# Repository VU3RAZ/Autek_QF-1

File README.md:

# Autek QF-1 Audio Filter: redraw, KiCad rebuild and analysis

A modern rework of the 1970s **Autek Research QF-1** tunable audio filter (peak / notch / low-pass, 250 Hz–2.5 kHz), made from the original 3-page manual.

| What | Where |
|---|---|
| Redrawn manual: full text plus vector schematics, hookup diagram and response curves | [`docs/Autek_QF-1_Instructions_Redrawn.pdf`](docs/Autek_QF-1_Instructions_Redrawn.pdf) |
| How the circuit works, stage by stage, with a performance rating | [`docs/QF1_How_It_Works.md`](docs/QF1_How_It_Works.md) |
| KiCad 7 projects: wired schematics plus routed 2-layer through-hole PCBs | [`kicad/`](kicad/) (see [`kicad/README.md`](kicad/README.md)) |
| Preview of both boards (schematics, copper, assembly) | [`docs/QF1_KiCad_Overview.pdf`](docs/QF1_KiCad_Overview.pdf) |
| Gerbers and drill files, ready for a PCB fab | `kicad/*/fab/*-gerbers.zip` |
| BOMs | `kicad/*/docs/*-BOM.csv` |
| LTspice / SPICE simulation: both boards and the complete unit, plus an `.asc` schematic generator | [`ltspice/`](ltspice/) |
| Python generators (PDF redraw, schematics, PCB placement and routing) | [`tools/`](tools/) |

Original manual scan: <https://vtda.org/docs/radio/Autek/Autek_QF-1.pdf>

## Boards

- **QF1_Main_Filter** (114 × 84 mm): two cascaded state-variable filter sections (TL072 × 3, replacing the µA747) and the U4 output amp (TL071, replacing the µA741). Board pins 1–21 keep the original numbering for front-panel wiring.
- **QF1_Amp_Supply** (92 × 64 mm): a Sallen-Key low-pass driver, a BC337/BC327 push-pull output, and a bridge-rectified supply fed from 12–15 VAC off-board.

Both boards are fully routed. DRC shows 0 errors. Netlist and pad connectivity are verified against the original circuit.

## Before ordering boards

See [`kicad/README.md`](kicad/README.md). In particular: the values chosen on test (R3/R5/R10/R11, R4/R9), C9/C10 left unfitted (DNP), the screw-terminal wire-entry orientation, and running ERC once in KiCad.

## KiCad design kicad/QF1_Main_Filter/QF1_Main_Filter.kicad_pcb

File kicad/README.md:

# Autek QF-1 Audio Filter: KiCad 7 projects

Two KiCad 7 projects recreated from the original Autek QF-1 manual schematics.
Each has a wired schematic laid out like the original drawing and a routed 2-layer through-hole PCB.

| Folder | Board | Size |
|---|---|---|
| `QF1_Main_Filter/` | Main filter board: two cascaded state-variable sections (U1 to U3) and output amp U4 | 114 x 84 mm |
| `QF1_Amp_Supply/` | Audio power amp (Sallen-Key + BC337/BC327 follower) and DC supply | 92 x 64 mm |

Each folder contains:
- `*.kicad_pro`, `*.kicad_sch`, `*.kicad_pcb`: open the `.kicad_pro` in KiCad 7 or later.
- `QF1.kicad_sym` and `sym-lib-table`: the project-local `B+` power symbol.
- `fab/*-gerbers.zip`: Gerbers (both copper layers, mask, silkscreen, outline), Excellon drill file and job file, ready to upload to a PCB fab.
- `docs/`: schematic PDF, top/bottom copper PDFs, assembly drawing, BOM (CSV) and DRC report.

## Checks performed
- Schematic connectivity: the netlist KiCad exports from each schematic was compared net by net against the circuit traced from the original manual. Both match exactly.
- PCB: every pad's net matches the original circuit. Freerouting routed 100% (0 unconnected pads, no vias needed). DRC shows **0 errors**; only cosmetic silkscreen-overlap warnings remain.
- KiCad 7's command-line tool has no ERC command. Run *Inspect > Electrical Rules Checker* once in your KiCad. Expect at most "dangling wire end" notes where the original drawing's rails end.

## Changes from the 1970s original
- **U1, U2, U3: TL072** (dual, 8-pin) replace the µA747 (dual, 14-pin). The A/B halves keep the original U1A to U3B roles and pin labels on the schematic. U4 and U101 are **TL071** in place of the µA741 (same pinout).
- **Q101/Q102: BC337/BC327** replace MPS6560/MPS6562, using the wide-pitch TO-92 footprint (CBE order, as on the original layout).
- **Supply:** the mains transformer, ON-OFF switch and line caps C107/C108 are **off-board**. J101 takes 12 to 15 VAC from the transformer secondary (outer ends of the original centre-tapped winding; CT unused) or from an AC wall adapter. A 4-diode bridge (D102 to D105) replaces the original 2-diode centre-tap rectifier. C106 is uprated to 35 V.
- **Added:** C13 (47 µF), C14 and C15 (100 nF) supply decoupling on the main board, and C109 (100 nF) on the amp board.
- **Mounting:** H101 is a plated M3 hole on GND, the original "direct RF ground to chassis through screw". The other holes are unplated.

## Values to confirm on test (as the original notes say)
- R3, R5, R10, R11: fitted as 3.3K. The original says 3.3K to 6.8K, chosen to match C2 to C5 (C2 to C5 matched to 1 %). 3.3K gives a 217 Hz–2.68 kHz tuning range, covering the manual's 250–2500 Hz; 4.7K would top out at 1.88 kHz. Set the R8 trim to about 3.3K to align section 2. R11 also sets the low-pass mode gain (U4 gain 30, +29.6 dB).
- R4, R9: fitted as 4.7K. The original says "chosen to match select. pot" and gives no value; 4.7K is an estimate from the circuit, so adjust for the selectivity range you want.
- C9, C10: no value on the original (in parallel with R17/R14). Footprints are provided and marked DNP.
- C7: "not included in QF-1" (QF-2 output). Marked DNP.
- C2 to C5 are read as .018 µF (C3 is partly illegible on the scan).

## Panel wiring (unchanged; board pin numbers are on the silkscreen)
J1 = board pins 1 to 7, J2 = board pins 8 to 19, J3 = pin 20 (GND), J4 = pin 21 (QF-1 out).
- 5 and 6 tied to the front SELECTIVITY wiper; 8 to the top of front SELECTIVITY and to the front FREQUENCY wiper; 9 to the top of front FREQUENCY.
- 13 and 16 tied to the rear SELECTIVITY wiper; 18 to the top of rear SELECTIVITY and to the rear FREQUENCY wiper; 15 to the top of rear FREQUENCY.
- Pots are dual 500K (front/rear sections); bottom terminals are left open. Clockwise rotation selects lower frequency.
- Function switch pole 1: common 12, PK 5, NTCH 10, LP 11. Pole 2: common 3, PK 19, NTCH 17, LP 14.
- Main board 21 goes to amp board IN; 20 and the amp board GND go to chassis; amp board B+ goes to main board 1.

## Please check before ordering boards
- **Screw terminal orientation:** J101/J102 are placed with the wire entry assumed on the deeper side of the KiCad footprint, so they face the board edges. Confirm in the 3D viewer.
- The routing is autorouted (Freerouting) and DRC-clean. Give it a visual once-over in KiCad and tidy any track you'd like shorter.

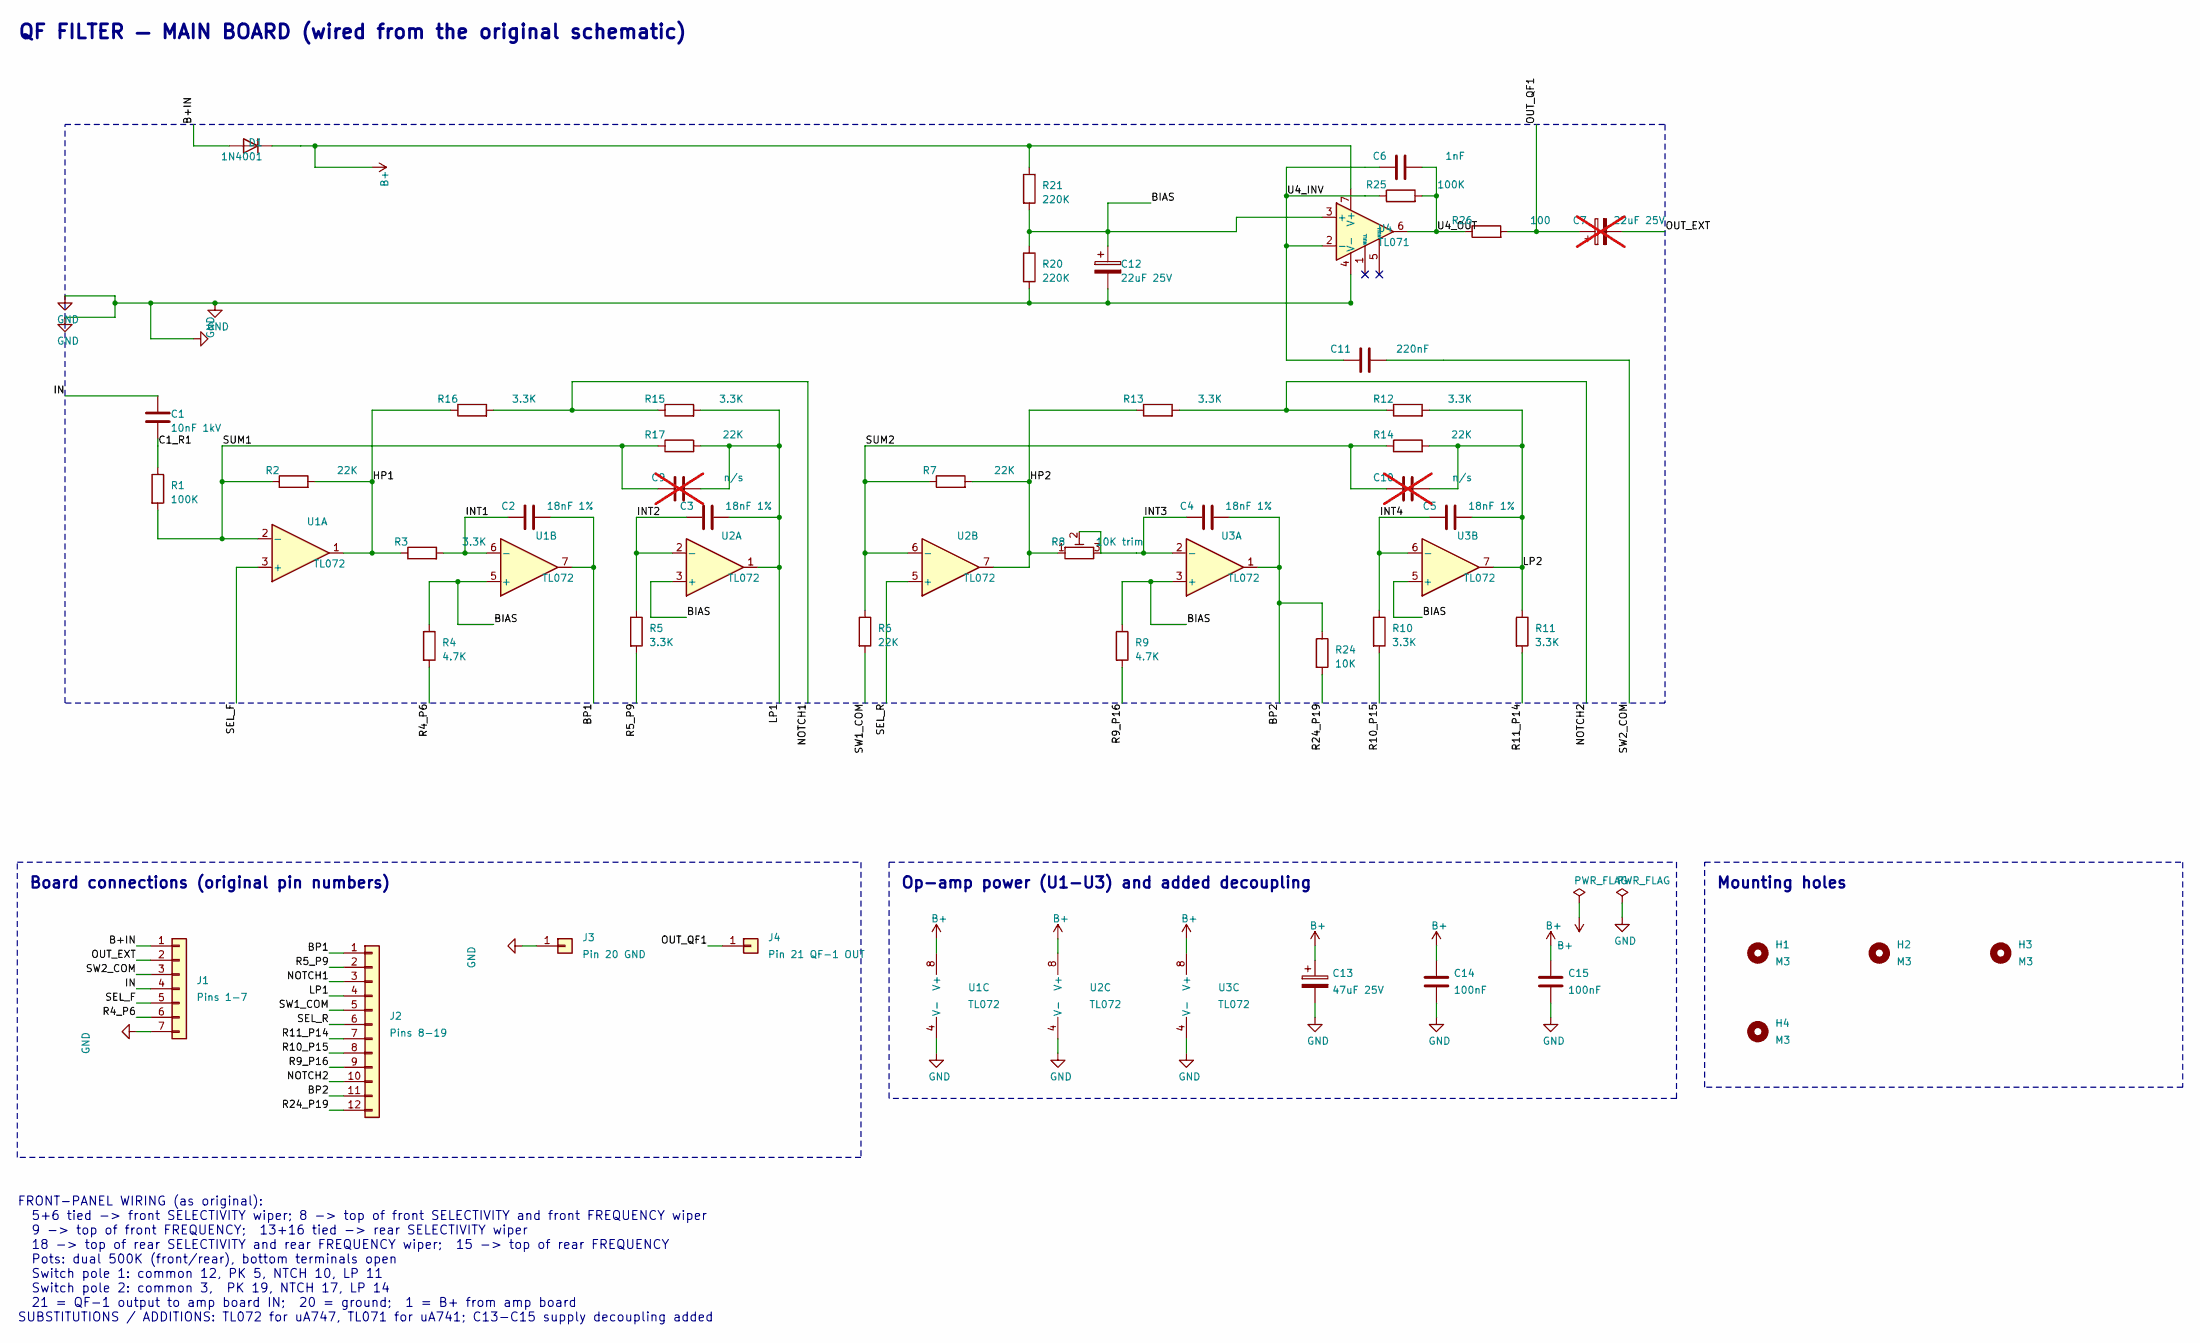
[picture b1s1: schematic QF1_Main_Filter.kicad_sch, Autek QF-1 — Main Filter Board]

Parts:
C1: 10nF 1kV; C_Disc_D7.5mm_W5.0mm_P5.00mm
C2, C3, C4, C5: 18nF 1%; C_Rect_L7.2mm_W3.5mm_P5.00mm_FKS2_FKP2_MKS2_MKP2
C6: 1nF; C_Disc_D5.0mm_W2.5mm_P5.00mm
C7: 22uF 25V; CP_Radial_D5.0mm_P2.00mm; not fitted
C9, C10: n/s; C_Disc_D5.0mm_W2.5mm_P5.00mm; not fitted
C11: 220nF; C_Rect_L7.2mm_W3.5mm_P5.00mm_FKS2_FKP2_MKS2_MKP2
C12: 22uF 25V; CP_Radial_D5.0mm_P2.00mm
C13: 47uF 25V; CP_Radial_D6.3mm_P2.50mm
C14, C15: 100nF; C_Disc_D5.0mm_W2.5mm_P5.00mm
D1: 1N4001; D_DO-41_SOD81_P10.16mm_Horizontal
H1, H2, H3, H4: M3; MountingHole_3.2mm_M3
J1: Pins 1-7; PinHeader_1x07_P2.54mm_Vertical
J2: Pins 8-19; PinHeader_1x12_P2.54mm_Vertical
J3: Pin 20 GND; PinHeader_1x01_P2.54mm_Vertical
J4: Pin 21 QF-1 OUT; PinHeader_1x01_P2.54mm_Vertical
R1, R25: 100K; R_Axial_DIN0207_L6.3mm_D2.5mm_P10.16mm_Horizontal
R2, R6, R7, R14, R17: 22K; R_Axial_DIN0207_L6.3mm_D2.5mm_P10.16mm_Horizontal
R3, R5, R10, R11, R12, R13, R15, R16: 3.3K; R_Axial_DIN0207_L6.3mm_D2.5mm_P10.16mm_Horizontal
R4, R9: 4.7K; R_Axial_DIN0207_L6.3mm_D2.5mm_P10.16mm_Horizontal
R8: 10K trim; Potentiometer_Bourns_3386P_Vertical
R20, R21: 220K; R_Axial_DIN0207_L6.3mm_D2.5mm_P10.16mm_Horizontal
R24: 10K; R_Axial_DIN0207_L6.3mm_D2.5mm_P10.16mm_Horizontal
R26: 100; R_Axial_DIN0207_L6.3mm_D2.5mm_P10.16mm_Horizontal
U1, U2, U3: TL072; DIP-8_W7.62mm
U4: TL071; DIP-8_W7.62mm

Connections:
B+: C13.1, C14.1, C15.1, D1.1 (K), R21.1, U1.8 (V+), U2.8 (V+), U3.8 (V+), U4.7 (V+)
B+IN: D1.2 (A), J1.1
BIAS: C12.1, R4.1, R9.1, R20.1, R21.2, U1.5 (+), U2.3 (+), U3.3 (+), U3.5 (+), U4.3 (+)
BP1: C2.2, J2.1, U1.7
BP2: C4.2, J2.11, R24.1, U3.1
C1_R1: C1.2, R1.1
GND: C12.2, C13.2, C14.2, C15.2, J1.7, J3.1, R20.2, U1.4 (V-), U2.4 (V-), U3.4 (V-), U4.4 (V-)
HP1: R2.2, R3.1, R16.1, U1.1
HP2: R7.2, R8.1, R13.1, U2.7
IN: C1.1, J1.4
INT1: C2.1, R3.2, U1.6 (-)
INT2: C3.1, R5.1, U2.2 (-)
INT3: C4.1, R8.2, R8.3, U3.2 (-)
INT4: C5.1, R10.1, U3.6 (-)
LP1: C3.2, C9.2, J2.4, R15.2, R17.2, U2.1
LP2: C5.2, C10.2, R11.1, R12.2, R14.2, U3.7
NOTCH1: J2.3, R15.1, R16.2
NOTCH2: J2.10, R12.1, R13.2
OUT_EXT: C7.2, J1.2
OUT_QF1: C7.1, J4.1, R26.2
R4_P6: J1.6, R4.2
R5_P9: J2.2, R5.2
R9_P16: J2.9, R9.2
R10_P15: J2.8, R10.2
R11_P14: J2.7, R11.2
R24_P19: J2.12, R24.2
SEL_F: J1.5, U1.3 (+)
SEL_R: J2.6, U2.5 (+)
SUM1: C9.1, R1.2, R2.1, R17.1, U1.2 (-)
SUM2: C10.1, R6.1, R7.1, R14.1, U2.6 (-)
SW1_COM: J2.5, R6.2
SW2_COM: C11.2, J1.3
U4_INV: C6.1, C11.1, R25.1, U4.2 (-)
U4_OUT: C6.2, R25.2, R26.1, U4.6

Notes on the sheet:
QF FILTER — MAIN BOARD (wired from the original schematic)
Board connections (original pin numbers)
Op-amp power (U1-U3) and added decoupling
Mounting holes
FRONT-PANEL WIRING (as original): 5+6 tied -> front SELECTIVITY wiper; 8 -> top of front SELECTIVITY and front FREQUENCY wiper 9 -> top of front FREQUENCY; 13+16 tied -> rear SELECTIVITY wiper 18 -> top of rear SELECTIVITY and rear FREQUENCY wiper; 15 -> top of rear FREQUENCY Pots: dual 500K (front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

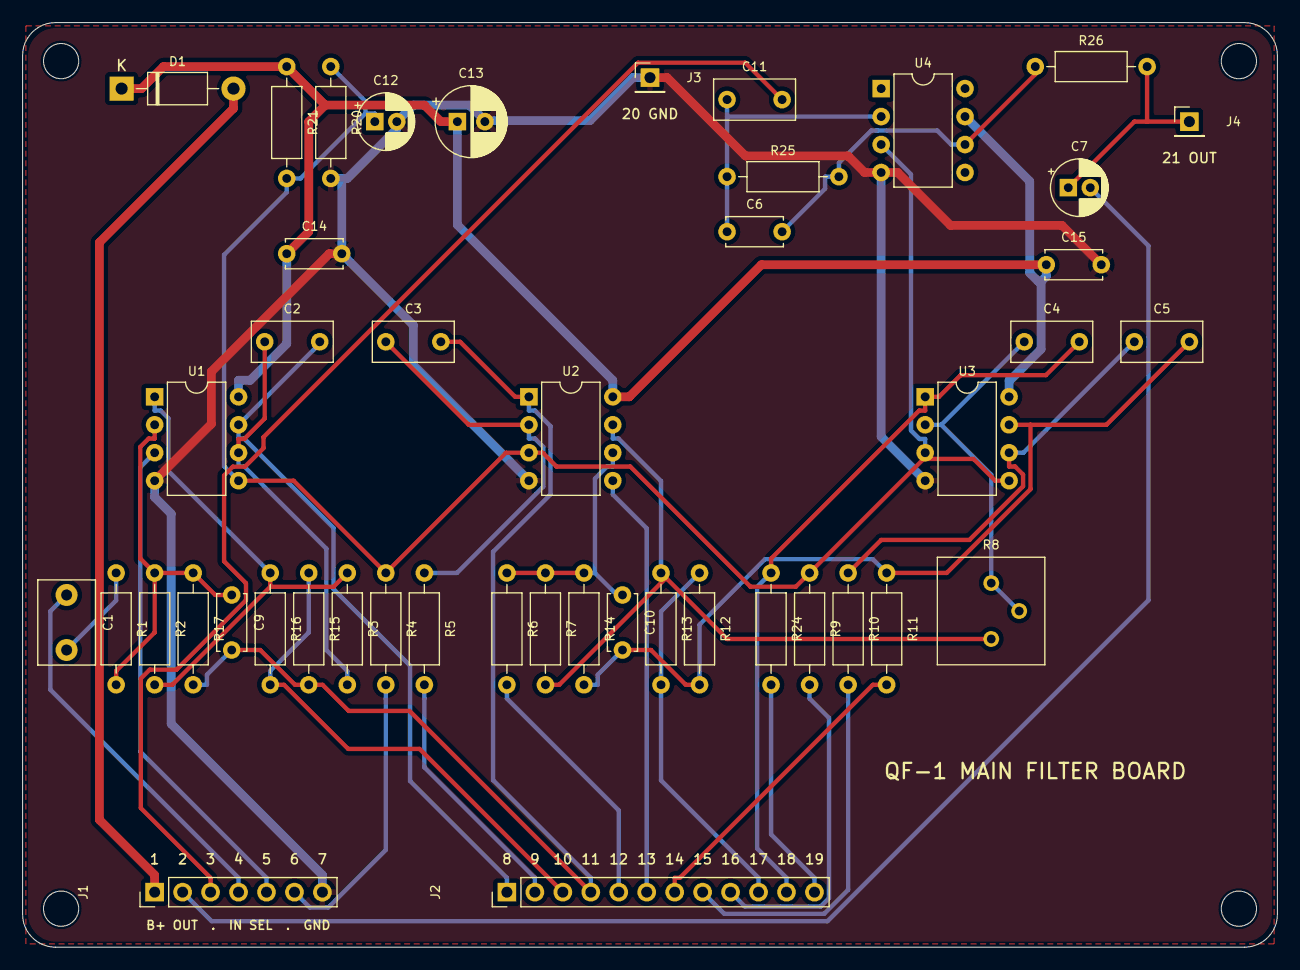
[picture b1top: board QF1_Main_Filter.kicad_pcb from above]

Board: 2 copper layers, 114.0 x 84.0 mm, 49 parts (0 on the bottom side), 34 nets.

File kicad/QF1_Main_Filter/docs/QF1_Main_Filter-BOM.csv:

Qty,References,Value,Footprint,Fit,Notes
1,C1,10nF 1kV,C_Disc_D7.5mm_W5.0mm_P5.00mm,fit,
4,C2 C3 C4 C5,18nF 1%,C_Rect_L7.2mm_W3.5mm_P5.00mm_FKS2_FKP2_MKS2_MKP2,fit,
1,C6,1nF,C_Disc_D5.0mm_W2.5mm_P5.00mm,fit,
1,C7,22uF 25V,CP_Radial_D5.0mm_P2.00mm,DNP,not included in QF-1
2,C9 C10,n/s,C_Disc_D5.0mm_W2.5mm_P5.00mm,DNP,value not given on original; optional
1,C11,220nF,C_Rect_L7.2mm_W3.5mm_P5.00mm_FKS2_FKP2_MKS2_MKP2,fit,
1,C12,22uF 25V,CP_Radial_D5.0mm_P2.00mm,fit,
1,C13,47uF 25V,CP_Radial_D6.3mm_P2.50mm,fit,added: B+ bulk decoupling (not on original)
1,C14,100nF,C_Disc_D5.0mm_W2.5mm_P5.00mm,fit,added: decoupling U1/U2
1,C15,100nF,C_Disc_D5.0mm_W2.5mm_P5.00mm,fit,added: decoupling U3/U4
1,D1,1N4001,D_DO-41_SOD81_P10.16mm_Horizontal,fit,
1,J1,Pins 1-7,PinHeader_1x07_P2.54mm_Vertical,fit,"Board pins 1 B+in, 2 out (not QF-1), 3 sw2 com, 4 input, 5/6 front select, 7 gnd"
1,J2,Pins 8-19,PinHeader_1x12_P2.54mm_Vertical,fit,J2 pin n = original board pin n+7
1,J3,Pin 20 GND,PinHeader_1x01_P2.54mm_Vertical,fit,
1,J4,Pin 21 QF-1 OUT,PinHeader_1x01_P2.54mm_Vertical,fit,
2,R1 R25,100K,R_Axial_DIN0207_L6.3mm_D2.5mm_P10.16mm_Horizontal,fit,
5,R2 R6 R7 R14 R17,22K,R_Axial_DIN0207_L6.3mm_D2.5mm_P10.16mm_Horizontal,fit,
3,R3 R5 R10,3.3K,R_Axial_DIN0207_L6.3mm_D2.5mm_P10.16mm_Horizontal,fit,"3.3K-6.8K, matched to C2-C5"
2,R4 R9,4.7K,R_Axial_DIN0207_L6.3mm_D2.5mm_P10.16mm_Horizontal,fit,select to match selectivity pot
1,R8,10K trim,Potentiometer_Bourns_3386P_Vertical,fit,alignment trim (rheostat)
1,R11,3.3K,R_Axial_DIN0207_L6.3mm_D2.5mm_P10.16mm_Horizontal,fit,3.3K-6.8K
4,R12 R13 R15 R16,3.3K,R_Axial_DIN0207_L6.3mm_D2.5mm_P10.16mm_Horizontal,fit,
2,R20 R21,220K,R_Axial_DIN0207_L6.3mm_D2.5mm_P10.16mm_Horizontal,fit,
1,R24,10K,R_Axial_DIN0207_L6.3mm_D2.5mm_P10.16mm_Horizontal,fit,
1,R26,100,R_Axial_DIN0207_L6.3mm_D2.5mm_P10.16mm_Horizontal,fit,
3,U1 U2 U3,TL072,DIP-8_W7.62mm,fit,replaces µA747
1,U4,TL071,DIP-8_W7.62mm,fit,replaces µA741

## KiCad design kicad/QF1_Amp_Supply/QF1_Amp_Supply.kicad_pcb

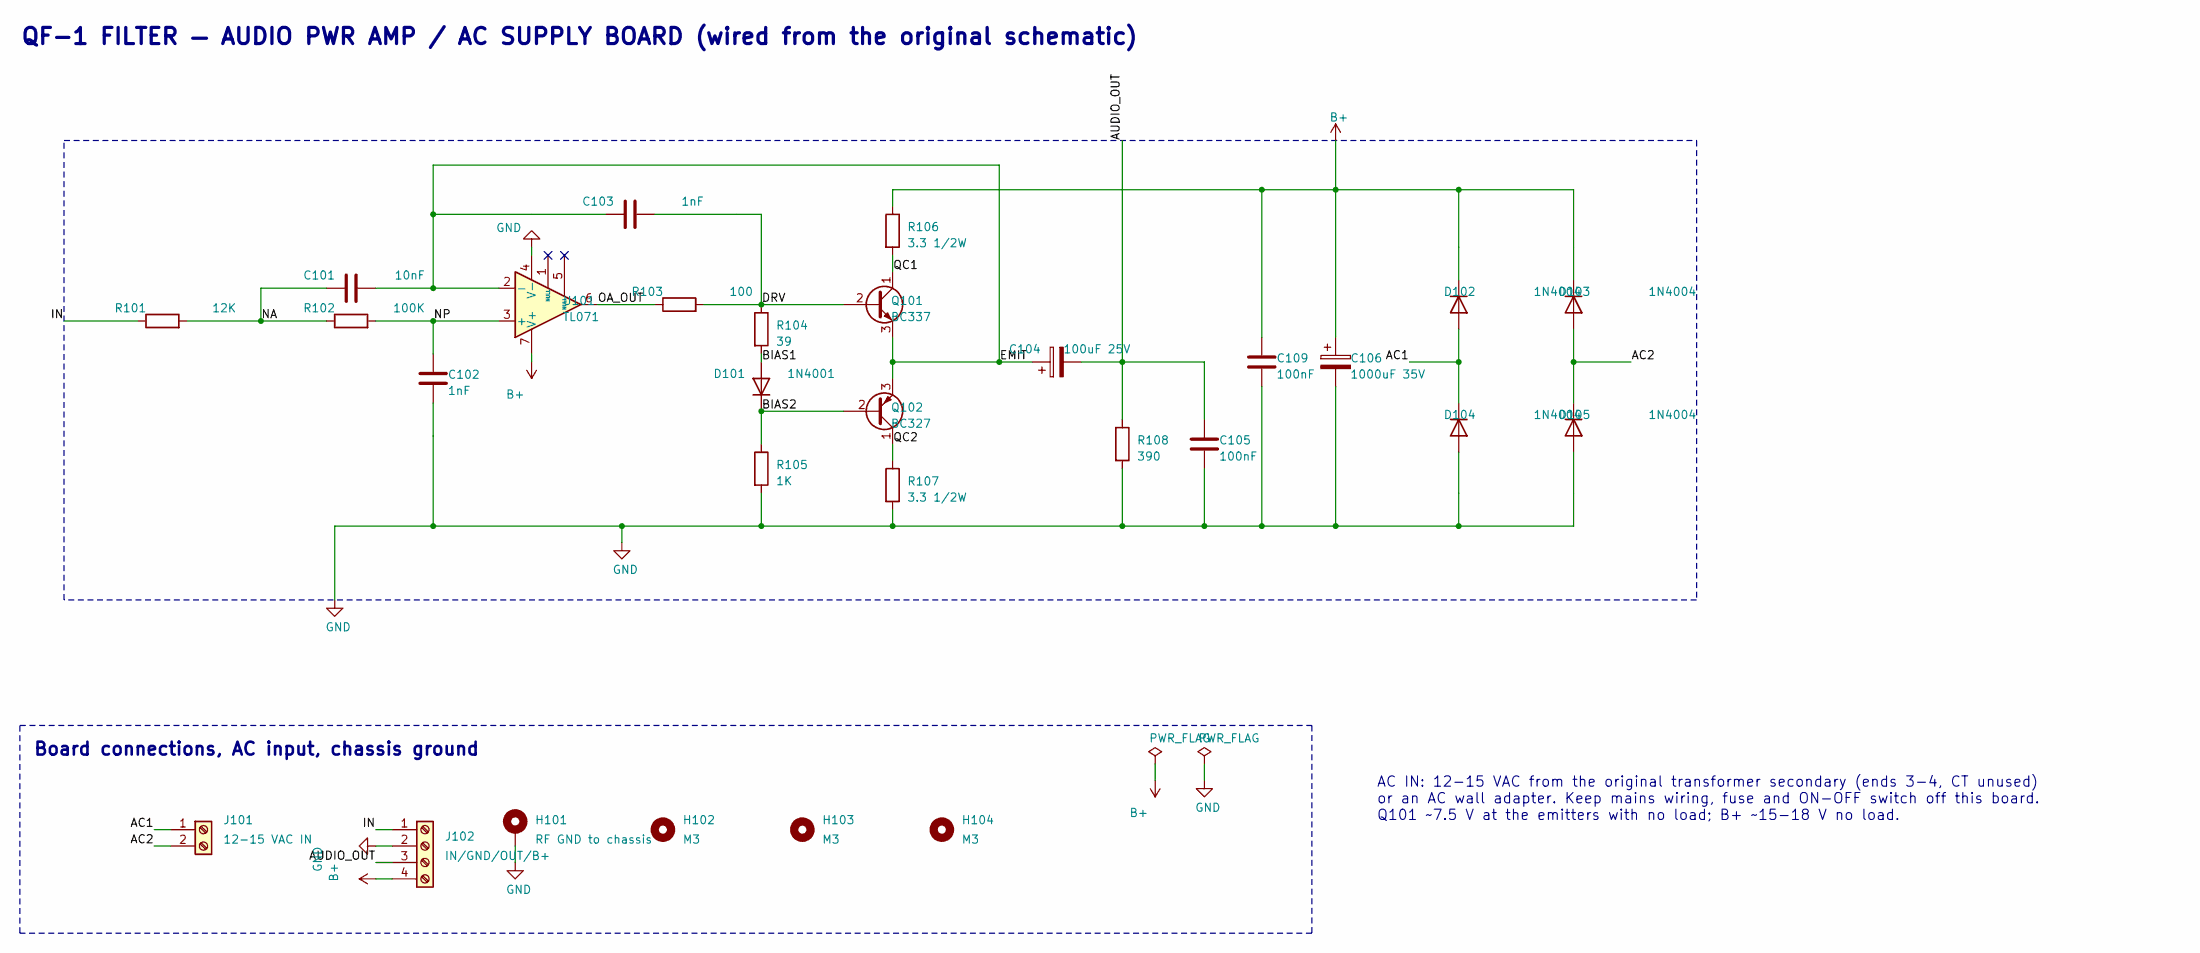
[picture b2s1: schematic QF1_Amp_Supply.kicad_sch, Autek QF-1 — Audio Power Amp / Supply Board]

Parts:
C101: 10nF; C_Rect_L7.2mm_W3.5mm_P5.00mm_FKS2_FKP2_MKS2_MKP2
C102, C103: 1nF; C_Disc_D5.0mm_W2.5mm_P5.00mm
C104: 100uF 25V; CP_Radial_D6.3mm_P2.50mm
C105, C109: 100nF; C_Disc_D5.0mm_W2.5mm_P5.00mm
C106: 1000uF 35V; CP_Radial_D12.5mm_P5.00mm
D101: 1N4001; D_DO-41_SOD81_P10.16mm_Horizontal
D102, D103, D104, D105: 1N4004; D_DO-41_SOD81_P10.16mm_Horizontal
H101: RF GND to chassis; MountingHole_3.2mm_M3_Pad_Via
H102, H103, H104: M3; MountingHole_3.2mm_M3
J101: 12-15 VAC IN; TerminalBlock_Phoenix_MKDS-1,5-2-5.08_1x02_P5.08mm_Horizont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
J102: IN/GND/OUT/B+; TerminalBlock_Phoenix_MKDS-1,5-4-5.08_1x04_P5.08mm_Horizont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
Q101: BC337; TO-92_Inline_Wide
Q102: BC327; TO-92_Inline_Wide
R101: 12K; R_Axial_DIN0207_L6.3mm_D2.5mm_P10.16mm_Horizontal
R102: 100K; R_Axial_DIN0207_L6.3mm_D2.5mm_P10.16mm_Horizontal
R103: 100; R_Axial_DIN0207_L6.3mm_D2.5mm_P10.16mm_Horizontal
R104: 39; R_Axial_DIN0207_L6.3mm_D2.5mm_P10.16mm_Horizontal
R105: 1K; R_Axial_DIN0207_L6.3mm_D2.5mm_P10.16mm_Horizontal
R106, R107: 3.3 1/2W; R_Axial_DIN0309_L9.0mm_D3.2mm_P12.70mm_Horizontal
R108: 390; R_Axial_DIN0207_L6.3mm_D2.5mm_P10.16mm_Horizontal
U101: TL071; DIP-8_W7.62mm

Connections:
AC1: D102.2 (A), D104.1 (K), J101.1
AC2: D103.2 (A), D105.1 (K), J101.2
AUDIO_OUT: C104.2, C105.1, J102.3, R108.1
B+: C106.1, C109.1, D102.1 (K), D103.1 (K), J102.4, R106.1, U101.7 (V+)
BIAS1: D101.2 (A), R104.2
BIAS2: D101.1 (K), Q102.2 (B), R105.1
DRV: C103.2, Q101.2 (B), R103.2, R104.1
EMIT: C101.2, C103.1, C104.1, Q101.3 (E), Q102.3 (E), U101.2 (-)
GND: C102.2, C105.2, C106.2, C109.2, D104.2 (A), D105.2 (A), H101.1, J102.2, R105.2, R107.2, R108.2, U101.4 (V-)
IN: J102.1, R101.1
NA: C101.1, R101.2, R102.1
NP: C102.1, R102.2, U101.3 (+)
OA_OUT: R103.1, U101.6
QC1: Q101.1 (C), R106.2
QC2: Q102.1 (C), R107.1

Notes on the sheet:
QF-1 FILTER — AUDIO PWR AMP / AC SUPPLY BOARD (wired from the original schematic)
Board connections, AC input, chassis ground
AC IN: 12-15 VAC from the original transformer secondary (ends 3-4, CT unused) or an AC wall adapter. Keep mains wiring, fuse and ON-OFF switch off this board. Q101 ~7.5 V at the emitters with no load; B+ ~15-18 V no load.

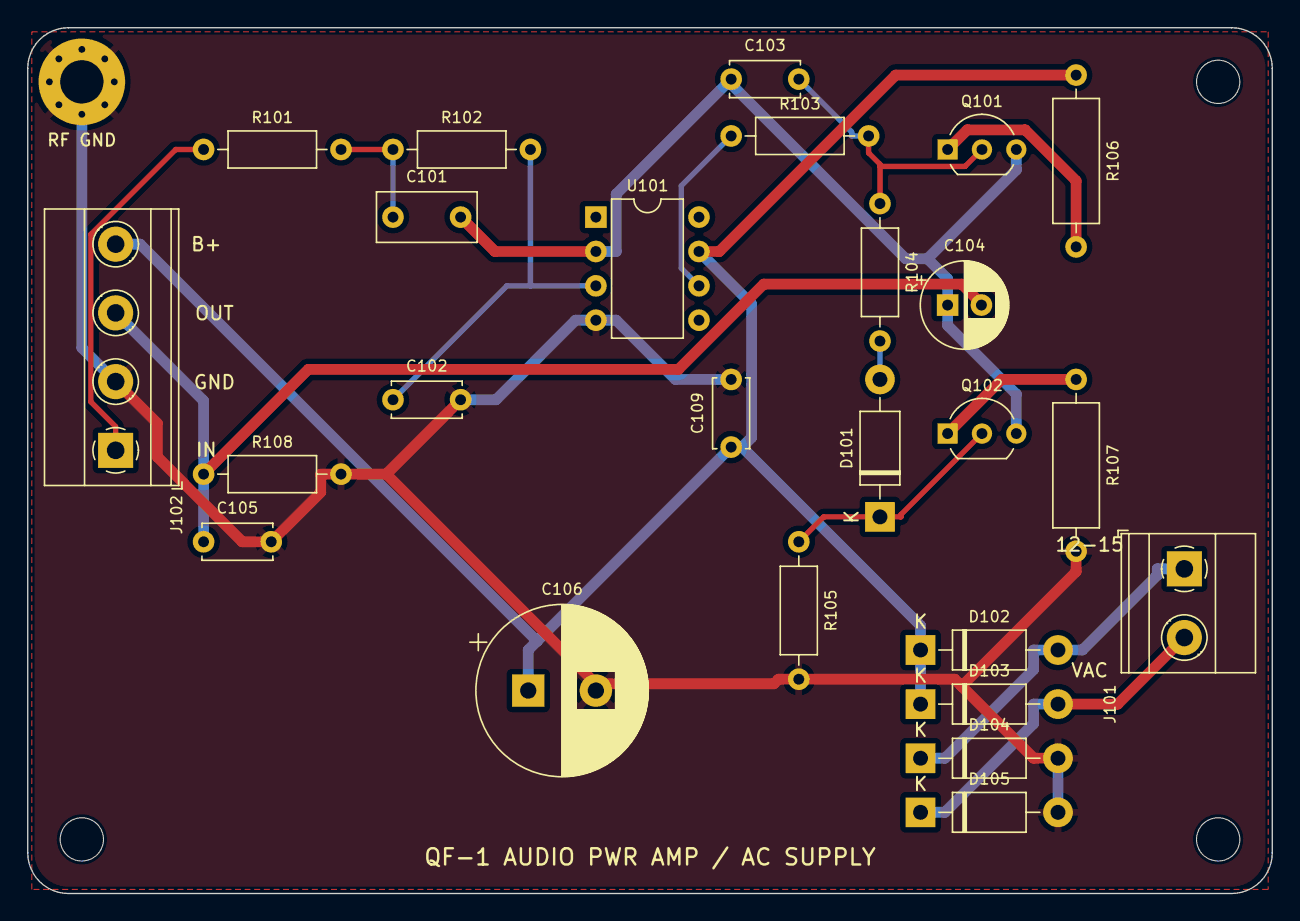
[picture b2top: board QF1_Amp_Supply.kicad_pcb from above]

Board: 2 copper layers, 92.0 x 64.0 mm, 29 parts (0 on the bottom side), 15 nets.

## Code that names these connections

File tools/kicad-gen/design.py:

"""Netlists for the two Autek QF-1 boards, as traced from the original schematics.
Each part: ref -> dict(sym, value, fp, pins={pin_number: net}, [dnp, note, group])."""

R07 = "Resistor_THT:R_Axial_DIN0207_L6.3mm_D2.5mm_P10.16mm_Horizontal"
R09 = "Resistor_THT:R_Axial_DIN0309_L9.0mm_D3.2mm_P12.70mm_Horizontal"
CFILM = "Capacitor_THT:C_Rect_L7.2mm_W3.5mm_P5.00mm_FKS2_FKP2_MKS2_MKP2"
CDISC = "Capacitor_THT:C_Disc_D5.0mm_W2.5mm_P5.00mm"
CHV = "Capacitor_THT:C_Disc_D7.5mm_W5.0mm_P5.00mm"
DIODE = "Diode_THT:D_DO-41_SOD81_P10.16mm_Horizontal"
DIP8 = "Package_DIP:DIP-8_W7.62mm"
TO92 = "Package_TO_SOT_THT:TO-92_Inline_Wide"


def R(a, b, val, fp=R07, **kw):
    return dict(sym="Device:R", value=val, fp=fp, pins={"1": a, "2": b}, **kw)


def C(a, b, val, fp=CFILM, **kw):
    return dict(sym="Device:C", value=val, fp=fp, pins={"1": a, "2": b}, **kw)


def CP(p, n, val, fp, **kw):
    return dict(sym="Device:C_Polarized", value=val, fp=fp, pins={"1": p, "2": n}, **kw)


def D(a, k, val="1N4001", **kw):
    return dict(sym="Device:D", value=val, fp=DIODE, pins={"1": k, "2": a}, **kw)


# ----------------------------------------------------------------- MAIN BOARD
MAIN = dict(name="QF1_Main_Filter", title="Autek QF-1 — Main Filter Board", parts={})
P = MAIN["parts"]
# board pins 1-7 (J1) and 8-19 (J2), 20 (J3), 21 (J4) keep the original numbering
P["J1"] = dict(sym="Connector_Generic:Conn_01x07", value="Pins 1-7",
               fp="Connector_PinHeader_2.54mm:PinHeader_1x07_P2.54mm_Vertical",
               pins={"1": "B+IN", "2": "OUT_EXT", "3": "SW2_COM", "4": "IN", "5": "SEL_F",
                     "6": "R4_P6", "7": "GND"},
               note="Board pins 1 B+in, 2 out (not QF-1), 3 sw2 com, 4 input, 5/6 front select, 7 gnd")
j2 = {8: "BP1", 9: "R5_P9", 10: "NOTCH1", 11: "LP1", 12: "SW1_COM", 13: "SEL_R", 14: "R11_P14",
      15: "R10_P15", 16: "R9_P16", 17: "NOTCH2", 18: "BP2", 19: "R24_P19"}
P["J2"] = dict(sym="Connector_Generic:Conn_01x12", value="Pins 8-19",
               fp="Connector_PinHeader_2.54mm:PinHeader_1x12_P2.54mm_Vertical",
               pins={str(k - 7): v for k, v in j2.items()},
               note="J2 pin n = original board pin n+7")
P["J3"] = dict(sym="Connector_Generic:Conn_01x01", value="Pin 20 GND",
               fp="Connector_PinHeader_2.54mm:PinHeader_1x01_P2.54mm_Vertical", pins={"1": "GND"})
P["J4"] = dict(sym="Connector_Generic:Conn_01x01", value="Pin 21 QF-1 OUT",
               fp="Connector_PinHeader_2.54mm:PinHeader_1x01_P2.54mm_Vertical", pins={"1": "OUT_QF1"})

# supply and bias
P["D1"] = D("B+IN", "B+")
P["R21"] = R("B+", "BIAS", "220K")
P["R20"] = R("BIAS", "GND", "220K")
P["C12"] = CP("BIAS", "GND", "22uF 25V", "Capacitor_THT:CP_Radial_D5.0mm_P2.00mm")
P["C13"] = CP("B+", "GND", "47uF 25V", "Capacitor_THT:CP_Radial_D6.3mm_P2.50mm",
              note="added: B+ bulk decoupling (not on original)")
P["C14"] = C("B+", "GND", "100nF", CDISC, note="added: decoupling U1/U2")
P["C15"] = C("B+", "GND", "100nF", CDISC, note="added: decoupling U3/U4")

# op-amps: TL072 replaces uA747 (A=1/2/3, B=5/6/7, V-=4, V+=8)
P["U1"] = dict(sym="Amplifier_Operational:TL072", value="TL072", note="replaces µA747", fp=DIP8,
               pins={"1": "HP1", "2": "SUM1", "3": "SEL_F", "5": "BIAS", "6": "INT1",
                     "7": "BP1", "4": "GND", "8": "B+"})
P["U2"] = dict(sym="Amplifier_Operational:TL072", value="TL072", note="replaces µA747", fp=DIP8,
               pins={"1": "LP1", "2": "INT2", "3": "BIAS", "5": "SEL_R", "6": "SUM2",
                     "7": "HP2", "4": "GND", "8": "B+"})
P["U3"] = dict(sym="Amplifier_Operational:TL072", value="TL072", note="replaces µA747", fp=DIP8,
               pins={"1": "BP2", "2": "INT3", "3": "BIAS", "5": "BIAS", "6": "INT4",
                     "7": "LP2", "4": "GND", "8": "B+"})
P["U4"] = dict(sym="Amplifier_Operational:TL071", value="TL071", note="replaces µA741", fp=DIP8,
               pins={"2": "U4_INV", "3": "BIAS", "6": "U4_OUT", "7": "B+", "4": "GND"})

# section 1
P["C1"] = C("IN", "C1_R1", "10nF 1kV", CHV)
P["R1"] = R("C1_R1", "SUM1", "100K")
P["R2"] = R("SUM1", "HP1", "22K")
P["R17"] = R("SUM1", "LP1", "22K")
P["C9"] = C("SUM1", "LP1", "n/s", CDISC, dnp=True, note="value not given on original; optional")
P["R16"] = R("HP1", "NOTCH1", "3.3K")
P["R15"] = R("NOTCH1", "LP1", "3.3K")
P["R3"] = R("HP1", "INT1", "3.3K", note="3.3K-6.8K, matched to C2-C5")
P["C2"] = C("INT1", "BP1", "18nF 1%")
P["R4"] = R("R4_P6", "BIAS", "4.7K", note="select to match selectivity pot")
P["R5"] = R("R5_P9", "INT2", "3.3K", note="3.3K-6.8K, matched to C2-C5")
P["C3"] = C("INT2", "LP1", "18nF 1%")
# section 2
P["R6"] = R("SW1_COM", "SUM2", "22K")
P["R7"] = R("SUM2", "HP2", "22K")
P["R14"] = R("SUM2", "LP2", "22K")
P["C10"] = C("SUM2", "LP2", "n/s", CDISC, dnp=True, note="value not given on original; optional")
P["R13"] = R("HP2", "NOTCH2", "3.3K")
P["R12"] = R("NOTCH2", "LP2", "3.3K")
P["R8"] = dict(sym="Device:R_Potentiometer_Trim", value="10K trim",
               fp="Potentiometer_THT:Potentiometer_Bourns_3386P_Vertical",
               pins={"1": "HP2", "2": "INT3", "3": "INT3"}, note="alignment trim (rheostat)")
P["C4"] = C("INT3", "BP2", "18nF 1%")
P["R24"] = R("BP2", "R24_P19", "10K")
P["R9"] = R("R9_P16", "BIAS", "4.7K", note="select to match selectivity pot")
P["R10"] = R("R10_P15", "INT4", "3.3K", note="3.3K-6.8K, matched to C2-C5")
P["C5"] = C("INT4", "LP2", "18nF 1%")
P["R11"] = R("LP2", "R11_P14", "3.3K", note="3.3K-6.8K")
# output amp
P["C11"] = C("SW2_COM", "U4_INV", "220nF")
P["R25"] = R("U4_INV", "U4_OUT", "100K")
P["C6"] = C("U4_INV", "U4_OUT", "1nF", CDISC)
P["R26"] = R("U4_OUT", "OUT_QF1", "100")
P["C7"] = CP("OUT_QF1", "OUT_EXT", "22uF 25V", "Capacitor_THT:CP_Radial_D5.0mm_P2.00mm",
             dnp=True, note="not included in QF-1")
for i in range(1, 5):
    P[f"H{i}"] = dict(sym="Mechanical:MountingHole", value="M3", fp="MountingHole:MountingHole_3.2mm_M3",
                      pins={})

# ----------------------------------------------------------------- AMP / SUPPLY BOARD
AMP = dict(name="QF1_Amp_Supply", title="Autek QF-1 — Audio Power Amp / Supply Board", parts={})
A = AMP["parts"]
A["J101"] = dict(sym="Connector:Screw_Terminal_01x02", value="12-15 VAC IN",
                 fp="TerminalBlock_Phoenix:TerminalBlock_Phoenix_MKDS-1,5-2-5.08_1x02_P5.08mm_Horizontal",
                 pins={"1": "AC1", "2": "AC2"}, note="from transformer secondary or AC adapter")
A["J102"] = dict(sym="Connector:Screw_Terminal_01x04", value="IN/GND/OUT/B+",
                 fp="TerminalBlock_Phoenix:TerminalBlock_Phoenix_MKDS-1,5-4-5.08_1x04_P5.08mm_Horizontal",
                 pins={"1": "IN", "2": "GND", "3": "AUDIO_OUT", "4": "B+"})
A["D102"] = D("AC1", "B+", "1N4004")
A["D103"] = D("AC2", "B+", "1N4004")
A["D104"] = D("GND", "AC1", "1N4004")
A["D105"] = D("GND", "AC2", "1N4004")
A["C106"] = CP("B+", "GND", "1000uF 35V", "Capacitor_THT:CP_Radial_D12.5mm_P5.00mm")
A["C109"] = C("B+", "GND", "100nF", CDISC, note="added: U101 decoupling")
A["R101"] = R("IN", "NA", "12K")
A["R102"] = R("NA", "NP", "100K")
A["C101"] = C("NA", "EMIT", "10nF")
A["C102"] = C("NP", "GND", "1nF", CDISC)
A["U101"] = dict(sym="Amplifier_Operational:TL071", value="TL071", note="replaces µA741", fp=DIP8,
                 pins={"2": "EMIT", "3": "NP", "6": "OA_OUT", "7": "B+", "4": "GND"})
A["C103"] = C("EMIT", "DRV", "1nF", CDISC)
A["R103"] = R("OA_OUT", "DRV", "100")
A["R104"] = R("DRV", "BIAS1", "39")
A["D101"] = D("BIAS1", "BIAS2", "1N4001")
A["R105"] = R("BIAS2", "GND", "1K")
A["Q101"] = dict(sym="Transistor_BJT:BC337", value="BC337", note="replaces MPS6560", fp=TO92,
                 pins={"1": "QC1", "2": "DRV", "3": "EMIT"})
A["Q102"] = dict(sym="Transistor_BJT:BC327", value="BC327", note="replaces MPS6562", fp=TO92,
                 pins={"1": "QC2", "2": "BIAS2", "3": "EMIT"})
A["R106"] = R("QC1", "B+", "3.3 1/2W", R09)
A["R107"] = R("QC2", "GND", "3.3 1/2W", R09)
A["C104"] = CP("EMIT", "AUDIO_OUT", "100uF 25V", "Capacitor_THT:CP_Radial_D6.3mm_P2.50mm")
A["R108"] = R("AUDIO_OUT", "GND", "390")
A["C105"] = C("AUDIO_OUT", "GND", "100nF", CDISC, note="RF bypass (.1-.22)")
A["H101"] = dict(sym="Mechanical:MountingHole_Pad", value="RF GND to chassis",
                 fp="MountingHole:MountingHole_3.2mm_M3_Pad_Via", pins={"1": "GND"})
for i in range(102, 105):
    A[f"H{i}"] = dict(sym="Mechanical:MountingHole", value="M3", fp="MountingHole:MountingHole_3.2mm_M3",
                      pins={})

BOARDS = [MAIN, AMP]
